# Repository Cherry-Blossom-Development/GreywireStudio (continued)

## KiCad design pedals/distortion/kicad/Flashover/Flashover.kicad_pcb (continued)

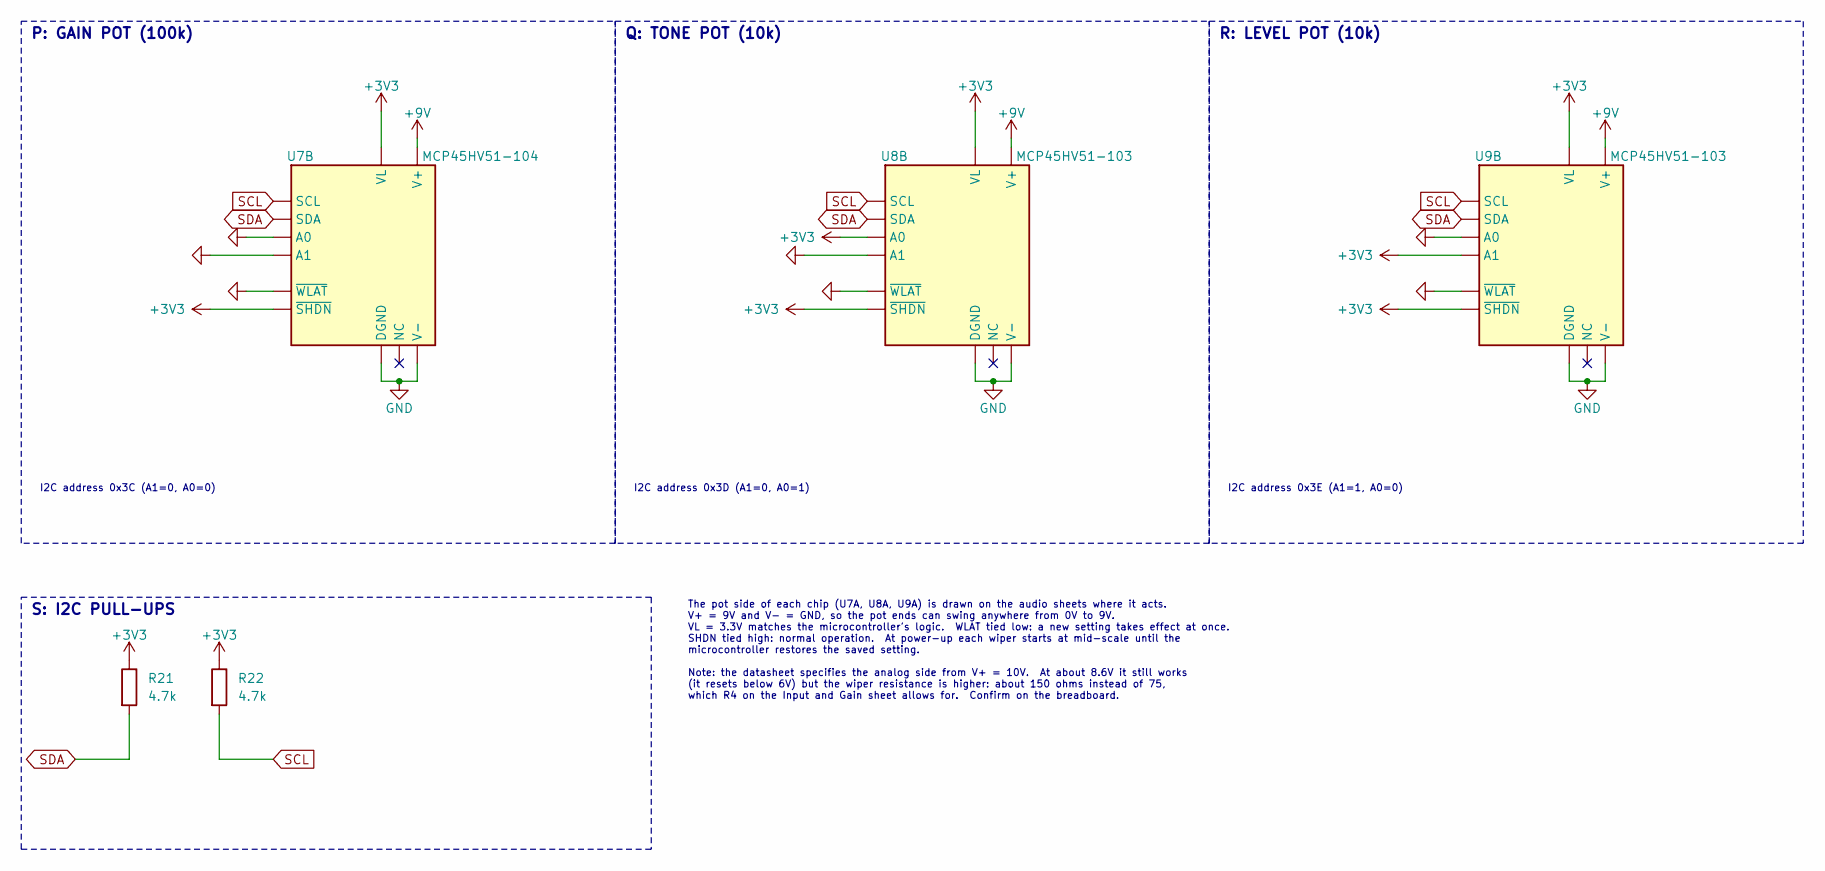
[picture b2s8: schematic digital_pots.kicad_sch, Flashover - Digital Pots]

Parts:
R21, R22: 4.7k; R_0805_2012Metric
U7: MCP45HV51-104; TSSOP-14_4.4x5mm_P0.65mm
U8, U9: MCP45HV51-103; TSSOP-14_4.4x5mm_P0.65mm

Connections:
+3V3: R21.1, R22.1, U7.1 (VL), U7.8 (~SHDN), U8.1 (VL), U8.5 (A0), U8.8 (~SHDN), U9.1 (VL), U9.3 (A1), U9.8 (~SHDN); also elsewhere on the board
+9V: U7.14 (V+), U8.14 (V+), U9.14 (V+); also elsewhere on the board
GND: U7.3 (A1), U7.5 (A0), U7.6 (~WLAT), U7.9 (DGND), U7.10 (V-), U8.3 (A1), U8.6 (~WLAT), U8.9 (DGND), U8.10 (V-), U9.5 (A0), U9.6 (~WLAT), U9.9 (DGND), U9.10 (V-); also elsewhere on the board
SCL: R22.2, U7.2 (SCL), U8.2 (SCL), U9.2 (SCL); also elsewhere on the board
SDA: R21.2, U7.4 (SDA), U8.4 (SDA), U9.4 (SDA); also elsewhere on the board

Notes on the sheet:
P: GAIN POT (100k)
I2C address 0x3C (A1=0, A0=0)
Q: TONE POT (10k)
I2C address 0x3D (A1=0, A0=1)
R: LEVEL POT (10k)
I2C address 0x3E (A1=1, A0=0)
S: I2C PULL-UPS
The pot side of each chip (U7A, U8A, U9A) is drawn on the audio sheets where it acts. V+ = 9V and V- = GND, so the pot ends can swing anywhere from 0V to 9V. VL = 3.3V matches the microcontroller's logic. WLAT tied low: a new setting takes effect at once. SHDN tied high: normal operation. At power-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

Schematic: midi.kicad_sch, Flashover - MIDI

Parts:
C41: 100n; C_0805_2012Metric
D43: 1N4148W; D_SOD-123
J5: MIDI In; Jack_3.5mm_CUI_SJ1-3523N_Horizontal
J6: MIDI Out; Jack_3.5mm_CUI_SJ1-3523N_Horizontal
R37: 220; R_0805_2012Metric
R38: 1k; R_0805_2012Metric
R39: 33 0.5W; R_2010_5025Metric
R40: 10; R_0805_2012Metric
U11: H11L1; SMDIP-6_W7.62mm

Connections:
+3V3: C41.1, R38.1, R39.2, U11.6; also elsewhere on the board
GND: C41.2, J6.S, U11.5; also elsewhere on the board
MIDI_RX: R38.2, U11.4; also elsewhere on the board
MIDI_TX: R40.1; also elsewhere on the board
unnamed: D43.2 (A), J5.T, U11.2
unnamed: D43.1 (K), R37.2, U11.1
unnamed: J5.R, R37.1
unnamed: J6.R, R39.1
unnamed: J6.T, R40.2

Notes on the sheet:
AD: MIDI IN
AE: MIDI OUT
Type A wiring: Tip = MIDI pin 5, Ring = MIDI pin 4, Sleeve = shield. The sleeve is left unconnected on the input, as the MIDI spec asks, to avoid ground loops. D43 protects the optocoupler if a reversed (Type B) cable is plugged in. The H11L1 runs from 3.3V and its output idles high, as the UART ex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
3.3V MIDI output, using the values in the MIDI Association's 3.3V update: 33 ohm from +3.3V to pin 4 (Ring) and 10 ohm from the UART to pin 5 (Tip). The sleeve is grounded on the output.
No hardware MIDI thru. The firmware passes on every message it receives and adds its own (merging, per the Linework Control Specification). If the pedal loses power the loop stops here; Switchyard detects the break. MIDI_RX and MIDI_TX go to UART0 on the microcontroller (GPIO1 and GPIO0).

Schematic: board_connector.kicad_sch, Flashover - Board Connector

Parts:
H1, H2: M3; MountingHole_3.2mm_M3
J7: To control board; PinSocket_2x10_P2.54mm_Vertical

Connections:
+3V3: J7.5; also elsewhere on the board
+5V: J7.1, J7.2; also elsewhere on the board
GAIN_A: J7.7; also elsewhere on the board
GAIN_B: J7.8; also elsewhere on the board
GAIN_SW: J7.9; also elsewhere on the board
GND: J7.3, J7.4, J7.6; also elsewhere on the board
LED_EN: J7.19; also elsewhere on the board
LED_SCL: J7.18; also elsewhere on the board
LED_SDA: J7.17; also elsewhere on the board
LEVEL_A: J7.13; also elsewhere on the board
LEVEL_B: J7.14; also elsewhere on the board
LEVEL_SW: J7.15; also elsewhere on the board
LINK_LED: J7.20; also elsewhere on the board
MODE_BTN: J7.16; also elsewhere on the board
TONE_A: J7.10; also elsewhere on the board
TONE_B: J7.11; also elsewhere on the board
TONE_SW: J7.12; also elsewhere on the board

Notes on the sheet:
AI: CONTROL BOARD CONNECTOR
2x10 socket, 2.54 mm. The control board's J8 header plugs in from above. It carries +5V (LED driver), +3V3 (pull-ups), the encoder and button signals, the LED driver bus and the Link LED.
AJ: MOUNTING
M3 holes for the standoffs that hold the control board.

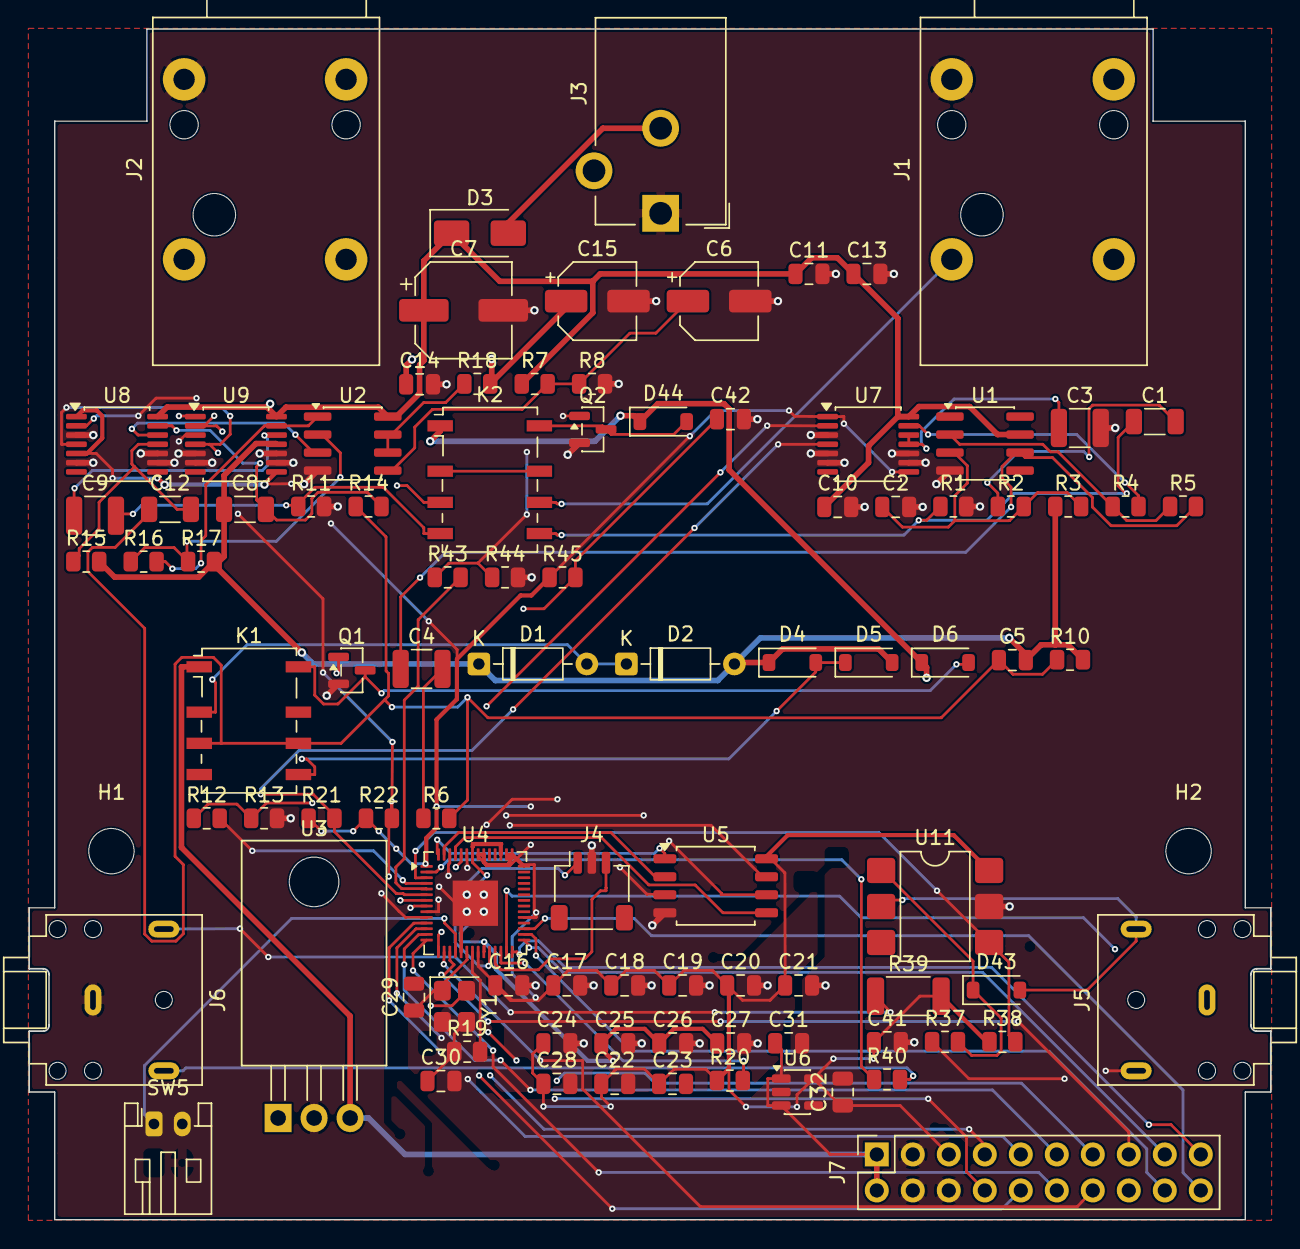
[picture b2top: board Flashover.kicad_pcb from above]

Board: 4 copper layers, 87.6 x 84.0 mm, 95 parts (0 on the bottom side), 72 nets.

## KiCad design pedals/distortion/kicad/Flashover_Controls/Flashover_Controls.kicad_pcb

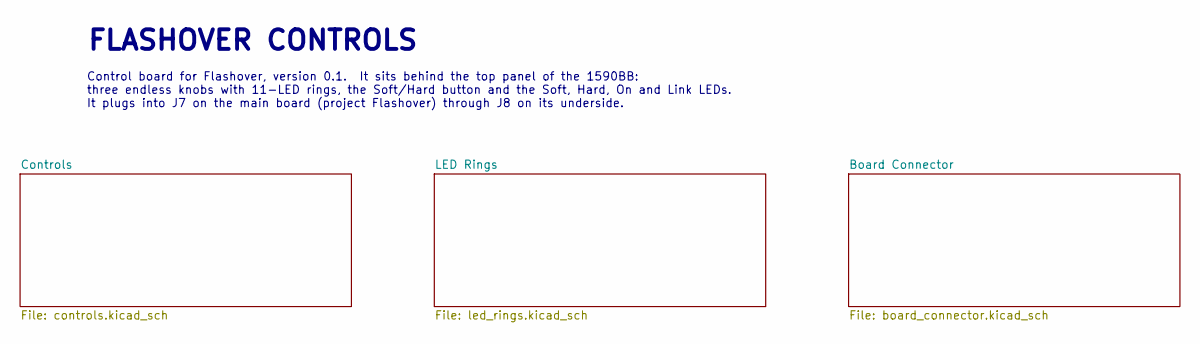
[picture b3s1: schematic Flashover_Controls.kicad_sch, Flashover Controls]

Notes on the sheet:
FLASHOVER CONTROLS
Control board for Flashover, version 0.1. It sits behind the top panel of the 1590BB: three endless knobs with 11-LED rings, the Soft/Hard button and the Soft, Hard, On and Link LEDs. It plugs into J7 on the main board (project Flashover) through J8 on its underside.

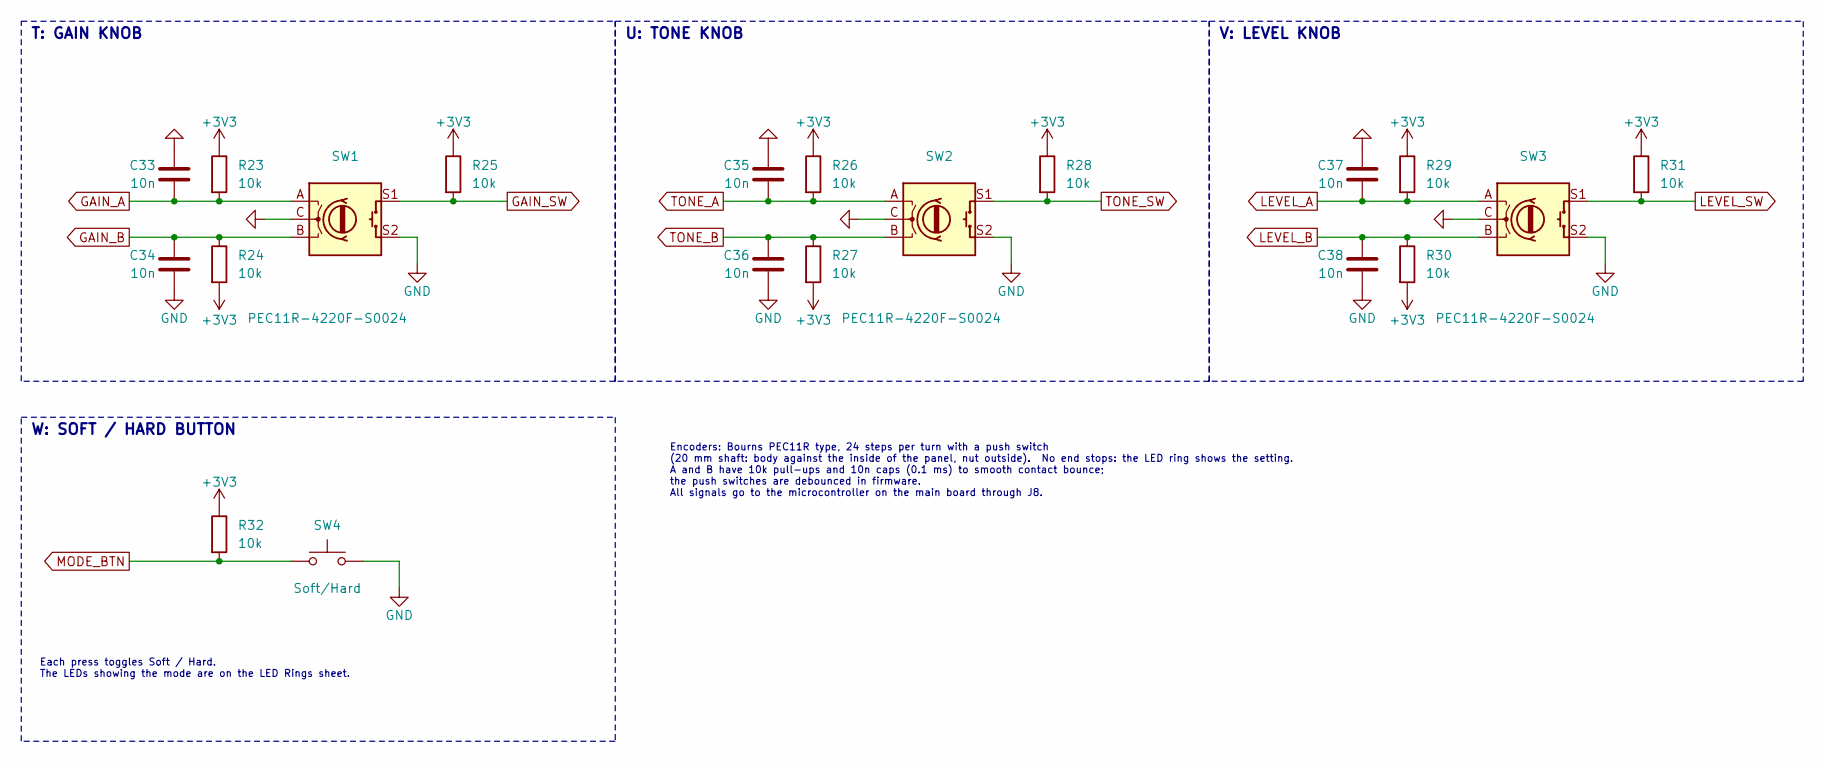
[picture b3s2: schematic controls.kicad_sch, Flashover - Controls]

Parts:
C33, C34, C35, C36, C37, C38: 10n; C_0805_2012Metric
R23, R24, R25, R26, R27, R28, R29, R30, R31, R32: 10k; R_0805_2012Metric
SW1, SW2, SW3: PEC11R-4220F-S0024; RotaryEncoder_Bourns_PEC11R-4xxxF-Sxxxx_Vertical
SW4: Soft/Hard; SW_PUSH_6mm_H13mm

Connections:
+3V3: R23.1, R24.2, R25.1, R26.1, R27.2, R28.1, R29.1, R30.2, R31.1, R32.1; also elsewhere on the board
GAIN_A: C33.2, R23.2, SW1.A; also elsewhere on the board
GAIN_B: C34.1, R24.1, SW1.B; also elsewhere on the board
GAIN_SW: R25.2, SW1.S1; also elsewhere on the board
GND: C33.1, C34.2, C35.1, C36.2, C37.1, C38.2, SW1.C, SW1.S2, SW2.C, SW2.S2, SW3.C, SW3.S2, SW4.2; also elsewhere on the board
LEVEL_A: C37.2, R29.2, SW3.A; also elsewhere on the board
LEVEL_B: C38.1, R30.1, SW3.B; also elsewhere on the board
LEVEL_SW: R31.2, SW3.S1; also elsewhere on the board
MODE_BTN: R32.2, SW4.1; also elsewhere on the board
TONE_A: C35.2, R26.2, SW2.A; also elsewhere on the board
TONE_B: C36.1, R27.1, SW2.B; also elsewhere on the board
TONE_SW: R28.2, SW2.S1; also elsewhere on the board

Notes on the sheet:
T: GAIN KNOB
U: TONE KNOB
V: LEVEL KNOB
W: SOFT / HARD BUTTON
Each press toggles Soft / Hard. The LEDs showing the mode are on the LED Rings sheet.
Encoders: Bourns PEC11R type, 24 steps per turn with a push switch (20 mm shaft: body against the inside of the panel, nut outside). No end stops: the LED ring shows the setting. A and B have 10k pull-ups and 10n caps (0.1 ms) to smooth contact bounce; the push switches are debounced in firmware. A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

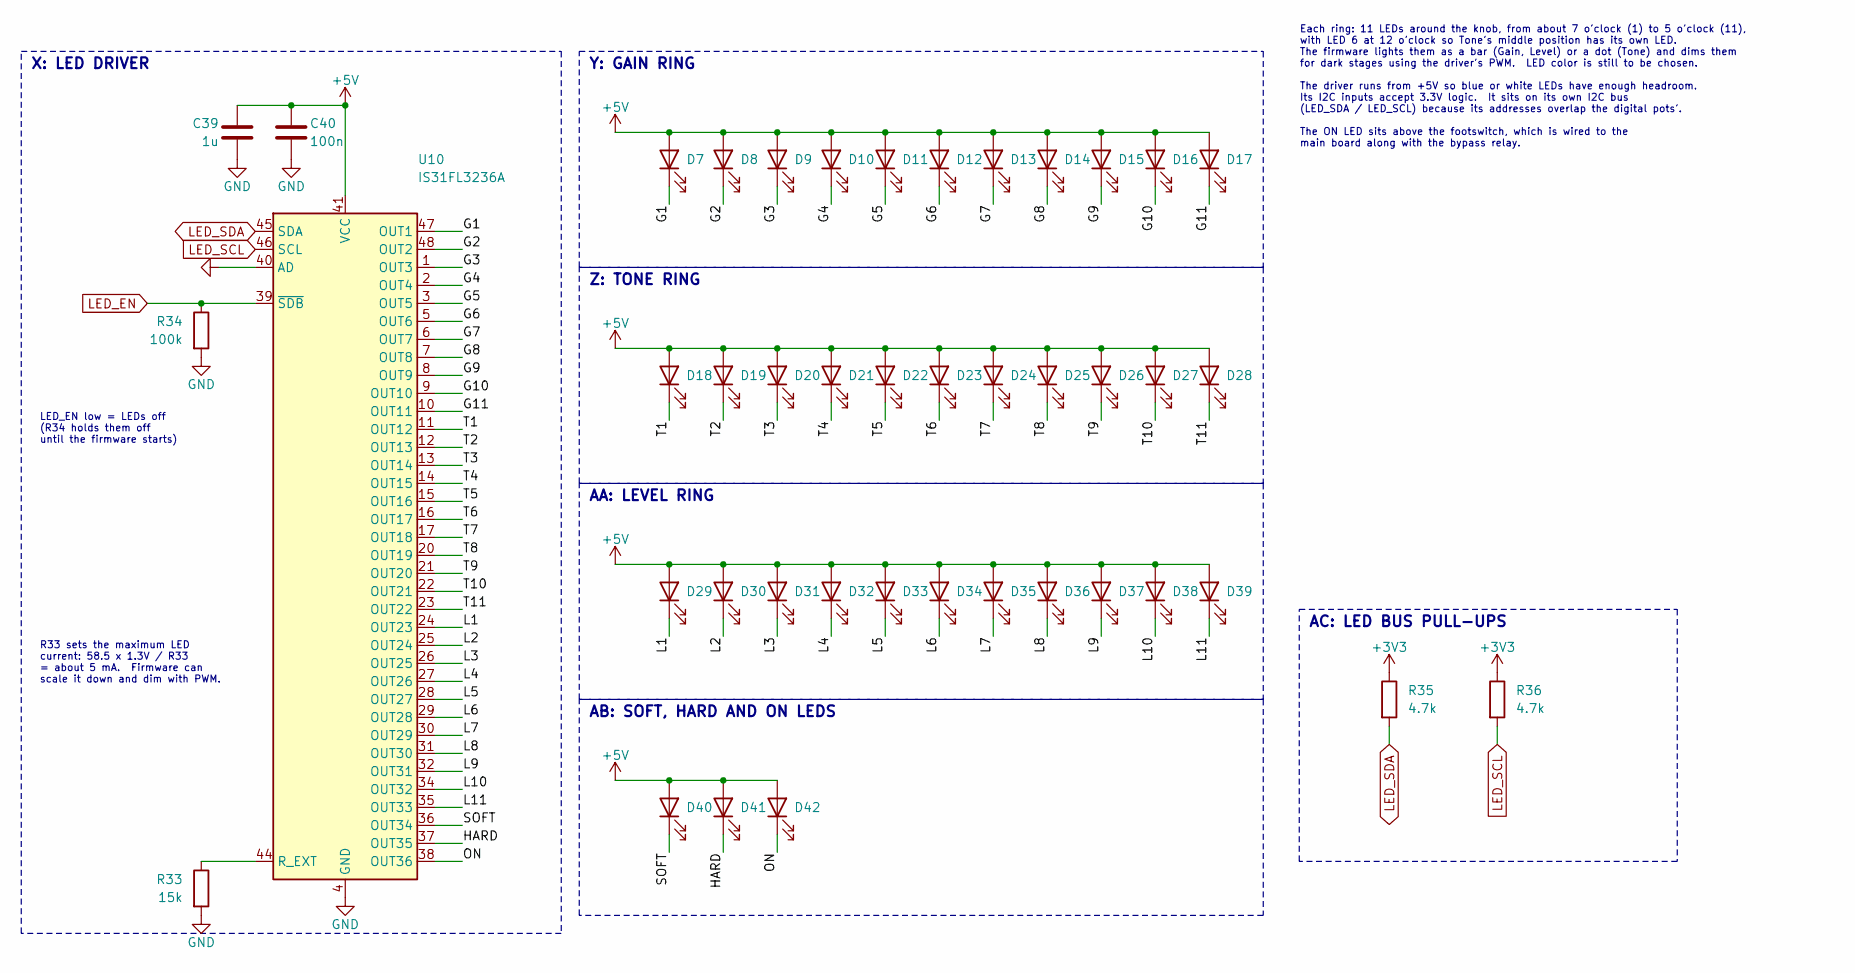
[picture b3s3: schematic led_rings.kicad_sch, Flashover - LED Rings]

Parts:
C39: 1u; C_0805_2012Metric
C40: 100n; C_0805_2012Metric
D7, D8, D9, D10, D11, D12, D13, D14, D15, D16, D17, D18, D19, D20, D21, D22, D23, D24, D25, D26, D27, D28, D29, D30, D31, D32, D33, D34, D35, D36, D37, D38, D39: LED; LED_0805_2012Metric
D40, D41, D42: LED; LED_D3.0mm
R33: 15k; R_0805_2012Metric
R34: 100k; R_0805_2012Metric
R35, R36: 4.7k; R_0805_2012Metric
U10: IS31FL3236A; TQFP-48-1EP_7x7mm_P0.5mm_EP4.11x4.11mm

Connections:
+3V3: R35.1, R36.1; also elsewhere on the board
+5V: C39.1, C40.1, D7.2 (A), D8.2 (A), D9.2 (A), D10.2 (A), D11.2 (A), D12.2 (A), D13.2 (A), D14.2 (A), D15.2 (A), D16.2 (A), D17.2 (A), D18.2 (A), D19.2 (A), D20.2 (A), D21.2 (A), D22.2 (A), D23.2 (A), D24.2 (A), D25.2 (A), D26.2 (A), D27.2 (A), D28.2 (A), D29.2 (A), D30.2 (A), D31.2 (A), D32.2 (A), D33.2 (A), D34.2 (A), D35.2 (A), D36.2 (A), D37.2 (A), D38.2 (A), D39.2 (A), D40.2 (A), D41.2 (A), D42.2 (A), U10.41 (VCC); also elsewhere on the board
/LED Rings/G1: D7.1 (K), U10.47 (OUT1)
/LED Rings/G2: D8.1 (K), U10.48 (OUT2)
/LED Rings/G3: D9.1 (K), U10.1 (OUT3)
/LED Rings/G4: D10.1 (K), U10.2 (OUT4)
/LED Rings/G5: D11.1 (K), U10.3 (OUT5)
/LED Rings/G6: D12.1 (K), U10.5 (OUT6)
/LED Rings/G7: D13.1 (K), U10.6 (OUT7)
/LED Rings/G8: D14.1 (K), U10.7 (OUT8)
/LED Rings/G9: D15.1 (K), U10.8 (OUT9)
/LED Rings/G10: D16.1 (K), U10.9 (OUT10)
/LED Rings/G11: D17.1 (K), U10.10 (OUT11)
/LED Rings/HARD: D41.1 (K), U10.37 (OUT35)
/LED Rings/L1: D29.1 (K), U10.24 (OUT23)
/LED Rings/L2: D30.1 (K), U10.25 (OUT24)
/LED Rings/L3: D31.1 (K), U10.26 (OUT25)
/LED Rings/L4: D32.1 (K), U10.27 (OUT26)
/LED Rings/L5: D33.1 (K), U10.28 (OUT27)
/LED Rings/L6: D34.1 (K), U10.29 (OUT28)
/LED Rings/L7: D35.1 (K), U10.30 (OUT29)
/LED Rings/L8: D36.1 (K), U10.31 (OUT30)
/LED Rings/L9: D37.1 (K), U10.32 (OUT31)
/LED Rings/L10: D38.1 (K), U10.34 (OUT32)
/LED Rings/L11: D39.1 (K), U10.35 (OUT33)
/LED Rings/ON: D42.1 (K), U10.38 (OUT36)
/LED Rings/SOFT: D40.1 (K), U10.36 (OUT34)
/LED Rings/T1: D18.1 (K), U10.11 (OUT12)
/LED Rings/T2: D19.1 (K), U10.12 (OUT13)
/LED Rings/T3: D20.1 (K), U10.13 (OUT14)
/LED Rings/T4: D21.1 (K), U10.14 (OUT15)
/LED Rings/T5: D22.1 (K), U10.15 (OUT16)
/LED Rings/T6: D23.1 (K), U10.16 (OUT17)
/LED Rings/T7: D24.1 (K), U10.17 (OUT18)
/LED Rings/T8: D25.1 (K), U10.20 (OUT19)
/LED Rings/T9: D26.1 (K), U10.21 (OUT20)
/LED Rings/T10: D27.1 (K), U10.22 (OUT21)
/LED Rings/T11: D28.1 (K), U10.23 (OUT22)
GND: C39.2, C40.2, R33.2, R34.2, U10.4 (GND), U10.18 (GND), U10.19 (GND), U10.33 (GND), U10.40 (AD), U10.42 (GND), U10.43 (GND), U10.49 (GND); also elsewhere on the board
LED_EN: R34.1, U10.39 (~SDB); also elsewhere on the board
LED_SCL: R36.2, U10.46 (SCL); also elsewhere on the board
LED_SDA: R35.2, U10.45 (SDA); also elsewhere on the board
unnamed: R33.1, U10.44 (R_EXT)

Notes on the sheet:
X: LED DRIVER
LED_EN low = LEDs off (R34 holds them off until the firmware starts)
R33 sets the maximum LED current: 58.5 x 1.3V / R33 = about 5 mA. Firmware can scale it down and dim with PWM.
Y: GAIN RING
Z: TONE RING
AA: LEVEL RING
AB: SOFT, HARD AND ON LEDS
Each ring: 11 LEDs around the knob, from about 7 o'clock (1) to 5 o'clock (11), with LED 6 at 12 o'clock so Tone's middle position has its own LED. The firmware lights them as a bar (Gain, Level) or a dot (Tone) and dims them for dark stages using the driver's PWM. LED color is still to be chosen. 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
AC: LED BUS PULL-UPS

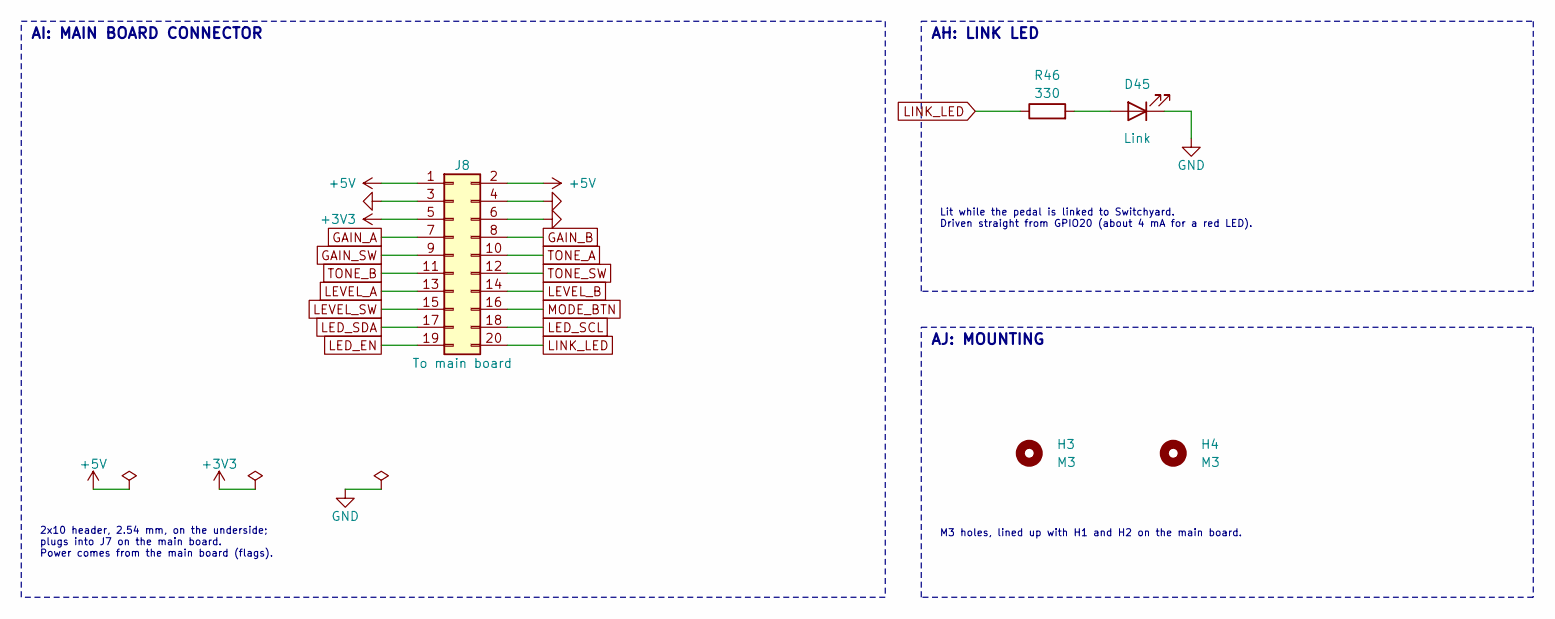
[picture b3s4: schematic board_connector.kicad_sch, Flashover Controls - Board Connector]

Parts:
D45: Link; LED_D3.0mm
H3, H4: M3; MountingHole_3.2mm_M3
J8: To main board; PinHeader_2x10_P2.54mm_Vertical
R46: 330; R_0805_2012Metric

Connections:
+3V3: J8.5; also elsewhere on the board
+5V: J8.1, J8.2; also elsewhere on the board
GAIN_A: J8.7; also elsewhere on the board
GAIN_B: J8.8; also elsewhere on the board
GAIN_SW: J8.9; also elsewhere on the board
GND: D45.1 (K), J8.3, J8.4, J8.6; also elsewhere on the board
LED_EN: J8.19; also elsewhere on the board
LED_SCL: J8.18; also elsewhere on the board
LED_SDA: J8.17; also elsewhere on the board
LEVEL_A: J8.13; also elsewhere on the board
LEVEL_B: J8.14; also elsewhere on the board
LEVEL_SW: J8.15; also elsewhere on the board
LINK_LED: J8.20, R46.1
MODE_BTN: J8.16; also elsewhere on the board
unnamed: D45.2 (A), R46.2
TONE_A: J8.10; also elsewhere on the board
TONE_B: J8.11; also elsewhere on the board
TONE_SW: J8.12; also elsewhere on the board

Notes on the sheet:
AI: MAIN BOARD CONNECTOR
2x10 header, 2.54 mm, on the underside; plugs into J7 on the main board. Power comes from the main board (flags).
AH: LINK LED
Lit while the pedal is linked to Switchyard. Driven straight from GPIO20 (about 4 mA for a red LED).
AJ: MOUNTING
M3 holes, lined up with H1 and H2 on the main board.

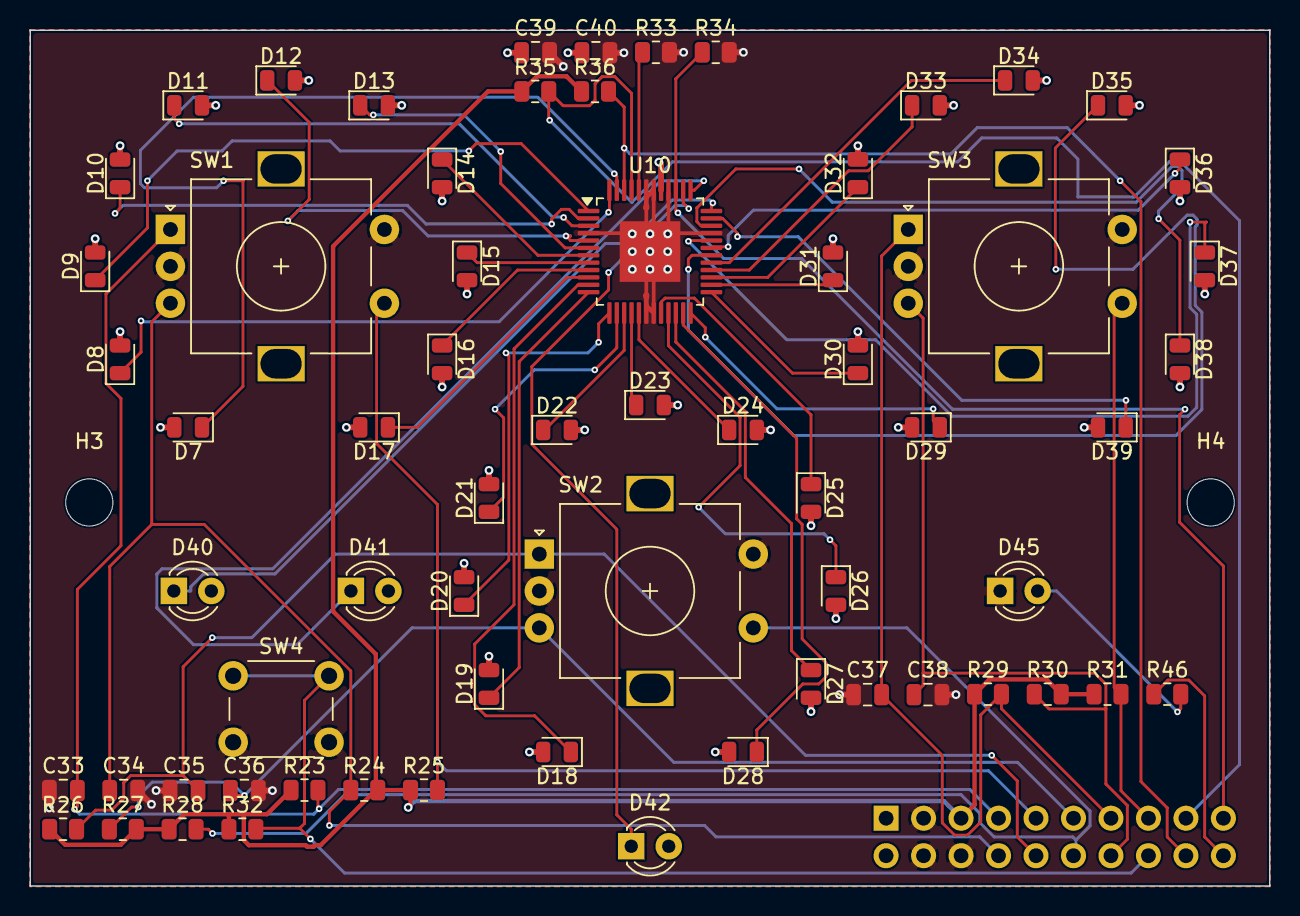
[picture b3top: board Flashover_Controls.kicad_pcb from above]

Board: 4 copper layers, 84.0 x 58.0 mm, 68 parts (1 on the bottom side), 55 nets.

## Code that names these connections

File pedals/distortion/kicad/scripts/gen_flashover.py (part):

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s = s2
s.box(8, 40, 58, 112, "A: INPUT")
s.box(60, 40, 112, 112, "B: GAIN STAGE")
s.label('global', 'FX_IN', 22, 63, 180, 'input')
s.wire((22, 63), (32, 63), (35, 63))
s.text("FX_IN comes from the input jack\nthrough the bypass relay\n(Bypass sheet).", 10, 80, size=1.0)
r1 = s.add("R1", "Device:R", "1M", 32, 70)
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s.wire(u1.p('2'), (63, 67), (63, 80), r5.p('1'))
s.wire(r5.p('2'), (82, 80), (82, 65))
s.wire(u1.p('6'), (82, 65), (92, 65))
s.label('hier', 'GAIN_OUT', 92, 65, 0, 'output')
r4 = s.add("R4", "Device:R", "330", 63, 86)
s.wire((63, 80), r4.p('1'))
rv1 = s.add("U7", POT, "MCP45HV51-104", 63, 95, unit=1, fields={'ref': (5, -1, 'left'), 'val': (5, 1, 'left')})
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       "Its control and power pins (U7B) are on the Digital Pots sheet.", 8, 118)

# =====================================================================
# Sheet 3: Clipping (Soft / Hard)
# =====================================================================
s3 = Sheet("Flashover - Clipping", 4, "Soft (germanium) or Hard (silicon) clipping, selected by relay K1")
s = s3
s.box(14, 36, 54, 66, "C: COUPLING")
s.box(54, 36, 140, 104, "D: SOFT / HARD CLIPPING")
s.label('hier', 'GAIN_OUT', 12, 48, 180, 'input')
c4 = s.add("C4", "Device:C", "1u", 20, 48, rot=90)
s.wire((12, 48), c4.p('1'))
r6 = s.add("R6", "Device:R", "10k", 29, 48, rot=90)
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s.wire((46, 48), c5.p('1'))
s.pwr('VB', 46, 58, rot=180)
s.wire((36, 48), (36, 42))
s.label('hier', 'CLIP', 36, 42, 0, 'output')
# unused contacts
s.nc(k1.p('4'))
s.nc(k1.p('7'))
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s.wire((113, 74), r13.p('1'))
s.pwr('GND', 113, 82)
s.wire(r12.p('2'), (124, 74))
s.label('global', 'HARD_SEL', 124, 74, 0, 'input')
s.text("Relay off = Soft, relay on = Hard.\n"
       "HARD_SEL comes from the microcontroller (controller sheet).\n"
       "R13 keeps the relay off (Soft) until the microcontroller starts.\n"
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s.box(14, 36, 46, 92, "E: TONE")
s.box(46, 36, 84, 92, "F: OUTPUT AMP")
s.box(84, 36, 138, 92, "G: LEVEL AND OUTPUT")
s.label('hier', 'CLIP', 12, 60, 180, 'input')
r14 = s.add("R14", "Device:R", "6.8k", 24, 54, rot=90)
c12 = s.add("C12", "Device:C", "22n", 24, 66, rot=90, fields={'ref': (0, 2, None), 'val': (0, 4, None)})
s.wire((12, 60), (18, 60))
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s.wire(rv3.p(PW), c9.p('1'))
r11 = s.add("R11", "Device:R", "100k", 114, 75)
s.wire(c9.p('2'), (114, 68), (122, 68))
s.label('global', 'FX_OUT', 122, 68, 0, 'output')
s.text("FX_OUT goes to the output jack\nthrough the bypass relay\n(Bypass sheet).", 117, 84, size=1.0)
s.wire((114, 68), r11.p('1'))
s.pwr('GND', 114, 78)
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    s.wire((x, y), (x - 4, y))
    s.label('local', nm, x - 4, y, 180)
# right-side pins: the ones used so far, the rest wait for later sheets
used = {'GPIO0': ('MIDI_TX', 'output'), 'GPIO1': ('MIDI_RX', 'input'), 'GPIO2': ('HARD_SEL', 'output'), 'GPIO3': ('FX_ON', 'output'), 'GPIO15': ('FOOTSW', 'input'), 'GPIO20': ('LINK_LED', 'output'), 'GPIO4': ('SDA', 'bidirectional'), 'GPIO5': ('SCL', 'output'),
        'GPIO6': ('GAIN_A', 'input'), 'GPIO7': ('GAIN_B', 'input'), 'GPIO8': ('GAIN_SW', 'input'),
        'GPIO9': ('TONE_A', 'input'), 'GPIO10': ('TONE_B', 'input'), 'GPIO11': ('TONE_SW', 'input'),
        'GPIO12': ('LEVEL_A', 'input'), 'GPIO13': ('LEVEL_B', 'input'), 'GPIO14': ('LEVEL_SW', 'input'),
        'GPIO16': ('MODE_BTN', 'input'), 'GPIO17': ('LED_EN', 'output'),
        'GPIO18': ('LED_SDA', 'bidirectional'), 'GPIO19': ('LED_SCL', 'output')}
for nm, num in pin_of.items():
    if not nm.startswith('GPIO'):
        continue
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s.text("2 MB: two firmware copies,\nsettings and 128 presets", 42, 94, size=1.0)

# --- M: 12 MHz crystal
s.label('local', 'XIN', 14, 106, 180)
y1 = s.add("Y1", "Device:Crystal_GND24", "12MHz", 33, 106, fields={'ref': (0, -6.5, None), 'val': (0, -4.5, None)})
s.wire((14, 106), (22, 106), y1.p('1'))
c29 = s.add("C29", "Device:C", "15p", 22, 109, fields=NV)
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c30 = s.add("C30", "Device:C", "15p", 39, 109)
s.pwr('GND', 39, 112)
s.wire(r19.p('2'), (56, 106))
s.label('local', 'XOUT', 56, 106, 0)
s.text("ABM8-272-T3, as on the Raspberry Pi Pico", 10, 120, size=1.0)

# --- O: SWD header
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r32 = s.add("R32", "Device:R", "10k", 30, 95)
s.pwr('+3V3', 30, 92)
s.wire(sw4.p('1'), (30, 98), (20, 98))
s.label('global', 'MODE_BTN', 20, 98, 180, 'output')
s.wire(sw4.p('2'), (50, 98), (50, 101))
s.pwr('GND', 50, 101)
s.text("Each press toggles Soft / Hard.\nThe LEDs showing the mode are on the LED Rings sheet.", 10, 110, size=1.0)
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s.add("C40", "Device:C", "100n", 34, 43)
s.pwr('GND', 28, 46)
s.pwr('GND', 34, 46)
s.label('global', 'LED_SDA', *drv.p(dp['SDA']), 180, 'bidirectional')
s.label('global', 'LED_SCL', *drv.p(dp['SCL']), 180, 'input')
x, y = drv.p(dp['AD'])
s.wire((x, y), (x - 4, y))
s.pwr('GND', x - 4, y, rot=270, hide_val=True)
x, y = drv.p(dp['~{SDB}'])
s.wire((x, y), (x - 6, y), (x - 12, y))
s.label('global', 'LED_EN', x - 12, y, 180, 'input')
s.add("R34", "Device:R", "100k", x - 6, y + 3, fields=NV)
s.pwr('GND', x - 6, y + 6)
x, y = drv.p(dp['R_EXT'])
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    s.add(ref, "Device:R", "4.7k", x, 106)
    s.pwr('+3V3', x, 103)
    s.wire((x, 109), (x, 111))
    s.label('global', net, x, 111, 270, 'bidirectional' if net == 'LED_SDA' else 'input')

# =====================================================================
# Sheet 9: MIDI in / out (3.5 mm TRS, Type A)
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r38 = s.add("R38", "Device:R", "1k", 76, 59)
s.pwr('+3V3', 76, 56)
s.wire(u11.p('4'), (76, 62), (84, 62))
s.label('global', 'MIDI_RX', 84, 62, 0, 'output')
s.text("Type A wiring: Tip = MIDI pin 5, Ring = MIDI pin 4, Sleeve = shield.\n"
       "The sleeve is left unconnected on the input, as the MIDI spec asks, to avoid ground loops.\n"
       "D43 protects the optocoupler if a reversed (Type B) cable is plugged in.\n"
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r40 = s.add("R40", "Device:R", "10", 74, 102, rot=90)
s.wire(j6.p('T'), r40.p('2'))
s.wire(r40.p('1'), (60, 102))
s.label('global', 'MIDI_TX', 60, 102, 180, 'input')
r39 = s.add("R39", "Device:R", "33 0.5W", 80, 107, fields={'ref': (-2, -1, 'right'), 'val': (-2, 1, 'right')})
s.wire(j6.p('R'), (80, 104))
s.pwr('+3V3', 80, 110, rot=180)
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s.text("No hardware MIDI thru.  The firmware passes on every message it receives\n"
       "and adds its own (merging, per the Linework Control Specification).\n"
       "If the pedal loses power the loop stops here; Switchyard detects the break.\n\n"
       "MIDI_RX and MIDI_TX go to UART0 on the microcontroller (GPIO1 and GPIO0).", 116, 40, size=1.0)

# =====================================================================
# Sheet 10: Bypass relay, jacks, footswitch and Link LED
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           fields={'ref': (-20, -3, None), 'val': (-20, -1, None)})
s.wire(j1.p('T'), (52, 52), k2.p('6'))
s.wire(k2.p('3'), (60, 46), j2.p('T'))
for pin, kind, nm in (('5', 'global', 'FX_IN'), ('7', 'local', 'BYPASS'), ('4', 'global', 'FX_OUT'), ('2', 'local', 'BYPASS')):
    x, y = k2.p(pin)
    s.wire((x, y), (x, y + 2))
    if kind == 'global':
        s.label('global', nm, x, y + 2, 270, 'output' if nm == 'FX_IN' else 'input')
    else:
        s.label('local', nm, x, y + 2, 270)
# coil, flyback diode and driver
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r44 = s.add("R44", "Device:R", "100k", 94, 83, fields={'ref': (-2, -1, 'right'), 'val': (-2, 1, 'right')})
s.pwr('GND', 94, 86)
s.wire(r43.p('2'), (106, 80))
s.label('global', 'FX_ON', 106, 80, 0, 'input')
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s.text("To avoid clicks, the firmware\nturns Level down for a few ms\nwhile the relay switches.", 100, 58, size=1.0)
# footswitch
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c42 = s.add("C42", "Device:C", "100n", 26, 107, fields={'ref': (-2, -1, 'right'), 'val': (-2, 1, 'right')})
s.pwr('GND', 26, 110)
s.wire(sw5.p('1'), (30, 104), (26, 104), (22, 104))
s.label('global', 'FOOTSW', 22, 104, 180, 'output')
s.wire(sw5.p('2'), (48, 104), (48, 107))
s.pwr('GND', 48, 107)
s.text("Soft-touch momentary switch on the panel, wired to a 2-pin\nJST PH connector.  Read by the firmware; C42 filters\nnoise picked up on the switch wires.", 10, 117, size=1.0)

# =====================================================================
# Board connectors (main board J7 <-> control board J8)
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s.text("2x10 header, 2.54 mm, on the underside;\nplugs into J7 on the main board.\n"
       "Power comes from the main board (flags).", 10, 94, size=1.0)
s.box(108, 36, 176, 66, "AH: LINK LED")
s.label('global', 'LINK_LED', 114, 46, 180, 'input')
r46 = s.add("R46", "Device:R", "330", 122, 46, rot=90)
s.wire((114, 46), r46.p('1'))
d45 = s.add("D45", "Device:LED", "Link", 132, 46, rot=180, fields={'ref': (0, -3, None), 'val': (0, 3, None)})
s.wire(r46.p('2'), d45.p('2'))
s.wire(d45.p('1'), (138, 46), (138, 49))
s.pwr('GND', 138, 49)
s.text("Lit while the pedal is linked to Switchyard.\nDriven straight from GPIO20 (about 4 mA for a red LED).", 110, 58, size=1.0)
s.box(108, 70, 176, 100, "AJ: MOUNTING")
_h = s.add("H3", "Mechanical:MountingHole", "M3", 120, 84, fields={'ref': (3, -1, 'left'), 'val': (3, 1, 'left')})
_h.no_bom = True
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subs = [  # (sheet, file, name, x, y, pins[(name, dir, side, dy)])
    (s10, "bypass.kicad_sch", "Bypass", 16, 40, []),
    (s2, "input_gain.kicad_sch", "Input and Gain", 66, 40, [("GAIN_OUT", "output", "R", 8)]),
    (s3, "clipping.kicad_sch", "Clipping", 116, 40, [("GAIN_OUT", "input", "L", 8), ("CLIP", "output", "R", 8)]),
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
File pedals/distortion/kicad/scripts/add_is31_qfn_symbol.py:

"""Add IS31FL3236A-QF (the QFN-44 package) to libraries/GreywireStudio.kicad_sym.

KiCad only has the TQFP-48 version (Driver_LED:IS31FL3236A-TQ). This copies it and renumbers the
pins to the QFN-44 package (Lumissil datasheet rev. I, pin description): OUT3-OUT18 = 1-16,
GND = 17 and 39, OUT19-OUT36 = 18-35, SDB 36, AD 37, VCC 38, R_EXT 40, SDA 41, SCL 42,
OUT1 43, OUT2 44, exposed pad 45 (GND). The TQFP's extra GND pins are dropped.
Run once with any Python 3; it does nothing if the symbol is already there.
"""
import copy
import kisym
from paths import LIB

FN = LIB + "GreywireStudio.kicad_sym"
NEW = "IS31FL3236A-QF"

def qfn_number(nm, tq):
    if nm.startswith("OUT"):
        n = int(nm[3:])
        return str(43 + n - 1 if n <= 2 else n - 2 if n <= 18 else n - 1)
    return {"~{SDB}": "36", "AD": "37", "VCC": "38", "R_EXT": "40", "SDA": "41", "SCL": "42",
            "GND": {"4": "17", "18": "39", "19": "45"}.get(tq)}[nm]

text = open(FN, encoding="utf-8").read()
if f'(symbol "{NEW}"' in text:
    print("already there")
    raise SystemExit
src = kisym.get_symbol("Driver_LED", "IS31FL3236A-TQ")   # flattened (it extends IS31FL3236-TQ)
src[1] = ("\"", NEW)
for e in src:
    if isinstance(e, list) and e[0] == "property":
        key = kisym.name(e)
        if key == "Value":
            e[2] = ("\"", NEW)
        elif key == "Footprint":
            e[2] = ("\"", "GreywireStudio:QFN-44-1EP_5x5mm_P0.4mm_EP2.45x2.45mm")
        elif key == "Description":
            e[2] = ("\"", "36-channel LED driver, I2C, QFN-44 5x5 mm (IS31FL3236A-QFLS2)")
    if isinstance(e, list) and e[0] == "symbol":
        e[1] = ("\"", kisym.name(e).replace("IS31FL3236A-TQ", NEW, 1))
        keep = []
        for p in e:
            if isinstance(p, list) and p[0] == "pin":
                nm = kisym.name(next(x for x in p if isinstance(x, list) and x[0] == "name"))
                num = next(x for x in p if isinstance(x, list) and x[0] == "number")
                q = qfn_number(nm, kisym.name(num))
                if q is None:
                    continue                      # a TQFP-only GND pin
                num[1] = ("\"", q)
            keep.append(p)
        e[:] = keep
block = kisym.dump(src, 1)
i = text.rstrip().rfind(")")
open(FN, "w", encoding="utf-8", newline="\n").write(text[:i].rstrip() + "\n\t" + block + "\n)\n")
print("added", NEW)
